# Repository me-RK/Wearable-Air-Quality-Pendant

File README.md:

Wearable Air Quality Pendant 🌬️
================================

A compact, battery-powered wearable device that continuously monitors air quality using TVOC detection. Get real-time feedback about your breathing environment through intuitive LED indicators and audio alerts.

Project Overview
-------------------

This DIY air quality monitor pendant uses professional-grade sensors to track Total Volatile Organic Compounds (TVOC) in real-time. Perfect for monitoring indoor air quality at home, office, or industrial environments.

### Key Features

-    **Real-time TVOC monitoring** using SGP40 sensor
-    **Ultra-low power design** with STM32U083KCU6 microcontroller
-    **Intuitive feedback** - Color-coded LEDs and musical alerts
-    **Wearable design** - Compact 32.5mm diameter pendant
-    **All-day battery life** with efficient power management
-    **Professional accuracy** with industrial-grade sensor

 Air Quality Classifications
------------------------------

| TVOC Level | Status | LED Color | Audio Alert |
| --- | --- | --- | --- |
| 0-200 | Good | 🟢 Green | Soft tone |
| 201-300 | Warning | 🟡 Yellow | Warning melody |
| 301-500 | Alarm | 🔴 Red | Urgent beeping |
| >500 | Error | 🔴 Flashing Red | Error tone |

 Hardware Components
-----------------------

### Main Components

-   **STM32U083KCU6** - Ultra-low-power microcontroller
-   **SGP40-D-R4** - Professional TVOC air quality sensor
-   **MCP73832T** - Li-Po battery charge controller
-   **ADPL44002** - Low-dropout voltage regulator
-   **EAST1616RGBA1** - RGB LEDs (4x)
-   **PKMCS0909E4000-R1** - Piezoelectric buzzer

### Power Management

-   Li-Po battery charging via USB-C
-   Regulated 2.5V supply for stable operation
-   Ultra-low power consumption for all-day use

📁 Repository Structure
-----------------------

```
├── Code/
│   └── Wearable_Air_Quality_Pendant/
│       ├── Wearable_Air_Quality_Pendant.ino
│       └── libraries/
├── PCB/
│   ├── Wearable-Air-Quality-Pendant.kicad_pro
│   ├── Schematic.pdf
│   └── Gerber_Files/
├── 3D_Models/
│   ├── Pendant_Top.stl
│   ├── Pendant_Bottom.stl
│   └── Assembly_Guide.pdf
├── Documentation/
│   ├── Circuit_Diagram.pdf
│   ├── Assembly_Instructions.pdf
│   └── BOM.csv
└── images/

```

🚀 Quick Start Guide
--------------------

### 1\. Hardware Assembly

1.  **Order PCB**: Use provided Gerber files
2.  **Solder components**: Follow the detailed BOM
3.  **3D print enclosure**: Use provided STL files
4.  **Assemble**: Insert PCB into printed enclosure

### 2\. Software Setup

1.  **Install Arduino IDE** (version 1.8.19 or newer)
2.  **Add STM32 board support**
3.  **Install required libraries**:
    -   DFRobot_SGP40
    -   PlayRtttl
    -   ptScheduler
4.  **Upload firmware** using ST-Link programmer

 Required Libraries
---------------------

Add these libraries through Arduino IDE Library Manager:

```
#include <DFRobot_SGP40.h>     // SGP40 sensor communication
#include <PlayRtttl.hpp>       // Musical tone generation
#include <ptScheduler.h>       // Non-blocking task scheduling

```

 Programming the Device
------------------------

### Hardware Requirements

-   **ST-Link V2 programmer** (required for STM32)
-   **USB-C cable** for power and charging
-   **3.3V power supply** during programming

### Upload Process

1.  Connect ST-Link to SWD pins (SWDIO, SWCLK)
2.  Select board: "STM32U0 series" in Arduino IDE
3.  Select programmer: "STM32CubeProgrammer (SWD)"
4.  Upload firmware

 PCB Specifications
---------------------

-   **Dimensions**: 32.5mm diameter
-   **Layers**: 2-layer PCB
-   **Thickness**: 1.6mm
-   **Components**: SMD (0603/0402 packages)
-   **Connector**: USB-C for charging

 3D Printing Guide
---------------------

### Print Settings

-   **Layer Height**: 0.2mm
-   **Infill**: 20%
-   **Supports**: Minimal (only for overhangs)
-   **Material**: PLA or PETG recommended

### Post-Processing

-   Light sanding for smooth finish
-   Ensure USB-C port alignment
-   Test fit before final assembly

Acknowledgments
------------------

-   **CircuitDigest** - Project development and documentation
-   **DFRobot** - SGP40 sensor library
-   **STMicroelectronics** - STM32 microcontroller support
-   **DigiKey** - Sponsors

Support
----------

-   **Detailed Tutorial**: [CircuitDigest Article](https://circuitdigest.com/videos/wearable-air-quality-pendant)
-   **Video Guide**: [YouTube Tutorial](https://youtube.com/watch?v=c5lP1kzYoBA)
-   **Issues**: Report bugs via GitHub Issues
-   **Discussion**: Join our community forum

Version History
-------------------

| Version | Date | Changes |
| --- | --- | --- |
| v1.0 | 2024-12 | Initial release |
| v1.1 | 2025-01 | Bug fixes, improved battery life |

* * * * *

**⭐ If this project helped you, please star the repository!**

**🔗 Related Projects:**

-   [Arduino Air Quality Monitor](https://github.com/Circuit-Digest/Arduino-Air-Quality-Monitor)
-   [IoT Air Quality System](https://github.com/Circuit-Digest/IoT-Air-Quality-System)

**📧 Contact:** support@circuitdigest.com

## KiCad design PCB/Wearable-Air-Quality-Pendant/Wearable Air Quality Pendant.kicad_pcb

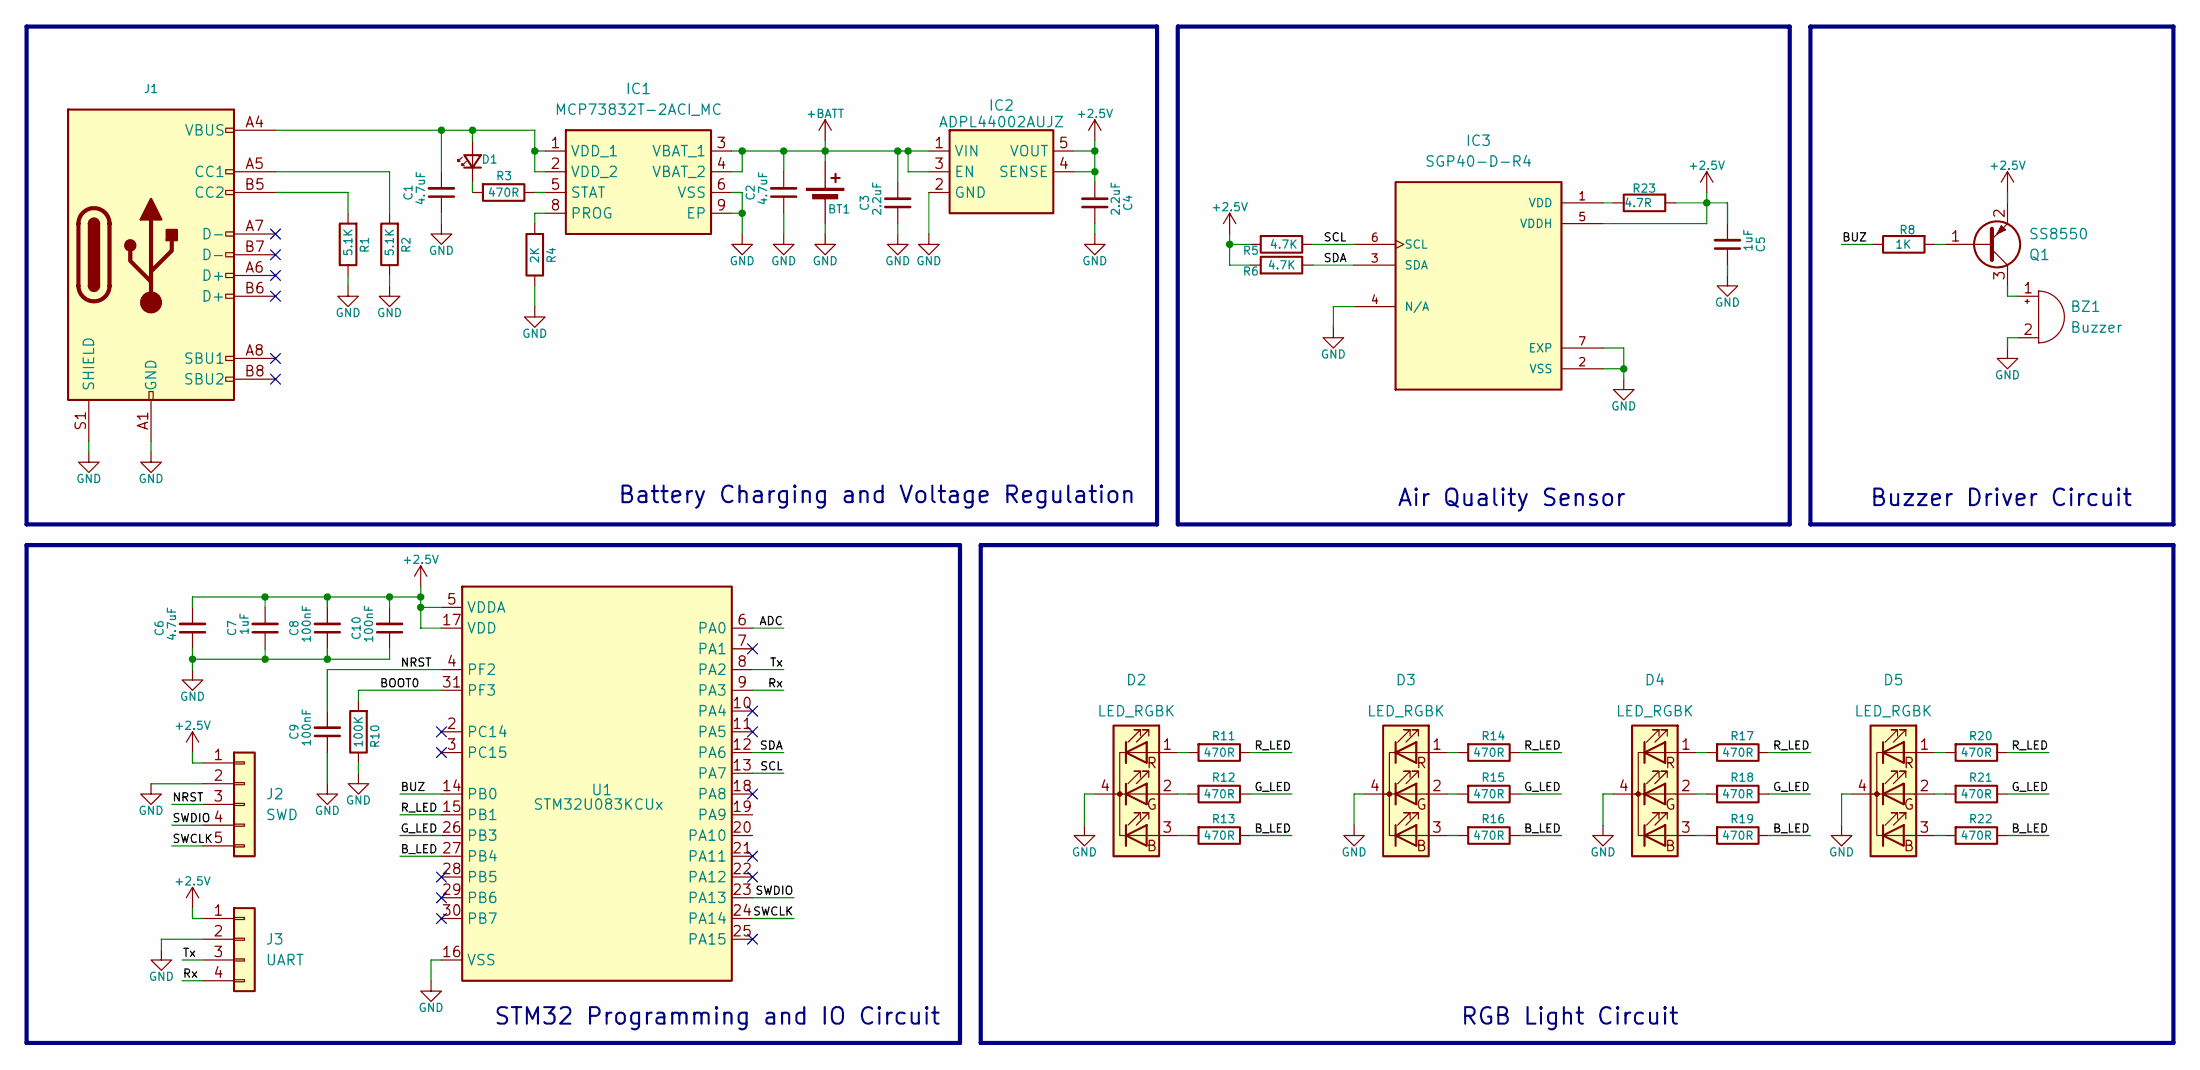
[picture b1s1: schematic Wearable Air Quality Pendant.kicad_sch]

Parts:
BT1: Battery_Cell; BAT_1060
BZ1: Buzzer; PKMCS0909E4000-R1_MUR
C1, C2, C6: 4.7uF; C_0603_1608Metric
C3, C4: 2.2uF; C_0603_1608Metric
C5, C7: 1uF; C_0603_1608Metric
C8, C9, C10: 100nF; C_0603_1608Metric
D1: LED_Small; LED_0603_1608Metric
D2, D3, D4, D5: LED_RGBK; EAST1616RGBA1
IC1: MCP73832T-2ACI_MC; SON50P300X200X100-9N-D; Mouser Part Number 579-MCP73832T-2ACIMC
IC2: ADPL44002AUJZ; SOT95P280X100-5N; Manufacturer_Part_Number ADPL44002AUJZ2.5-R7
IC3: SGP40-D-R4; XCDR_SGP40-D-R4; PARTREV 1.2
J1: USB_C_Receptacle_USB2.0_16P; USB_C_Receptacle_Palconn_UTC16-G
J2: SWD; PinHeader_1x06_P1.27mm_Vertical
J3: UART; PinHeader_1x04_P1.27mm_Vertical
Q1: SS8550; SOT-23
R1, R2: 5.1K; R_0603_1608Metric
R3, R11, R12, R13, R14, R15, R16, R17, R18, R19, R20, R21, R22: 470R; R_0603_1608Metric
R4: 2K; R_0603_1608Metric
R5, R6: 4.7K; R_0603_1608Metric
R8: 1K; R_0603_1608Metric
R10: 100K; R_0603_1608Metric
R23: 4.7R; R_0805_2012Metric
U1: STM32U083KCUx; QFN-32-1EP_5x5mm_P0.5mm_EP3.45x3.45mm

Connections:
+2.5V: C4.2, C5.2, C6.2, C7.2, C8.2, C10.2, IC2.4 (SENSE), IC2.5 (VOUT), IC3.5 (VDDH), J2.1, J3.1, Q1.2 (E), R5.2, R6.2, R23.2, U1.1 (VDD), U1.5 (VDDA), U1.17 (VDD)
+BATT: BT1.P (+), C2.2, C3.2, IC1.3 (VBAT_1), IC1.4 (VBAT_2), IC2.1 (VIN), IC2.3 (EN)
/ADC: U1.6 (PA0)
/BOOT0: R10.2, U1.31 (PF3)
/BUZ: R8.1, U1.14 (PB0)
/B_LED: R13.1, R16.1, R19.1, R22.1, U1.27 (PB4)
/G_LED: R12.1, R15.1, R18.1, R21.1, U1.26 (PB3)
/NRST: C9.2, J2.3, U1.4 (PF2)
/R_LED: R11.1, R14.1, R17.1, R20.1, U1.15 (PB1)
/Rx: J3.4, U1.9 (PA3)
/SCL: IC3.6 (SCL), R5.1, U1.13 (PA7)
/SDA: IC3.3 (SDA), R6.1, U1.12 (PA6)
/SWCLK: J2.5, U1.24 (PA14)
/SWDIO: J2.4, U1.23 (PA13)
/Tx: J3.3, U1.8 (PA2)
GND: BT1.N (-), BZ1.2 (-), C1.1, C2.1, C3.1, C4.1, C5.1, C6.1, C7.1, C8.1, C9.1, C10.1, D2.4 (K), D3.4 (K), D4.4 (K), D5.4 (K), IC1.6 (VSS), IC1.9 (EP), IC2.2 (GND), IC3.2 (VSS), IC3.4 (N/A), IC3.7 (EXP), J1.A1 (GND), J1.A12 (GND), J1.B1 (GND), J1.B12 (GND), J1.S1 (SHIELD), J2.2, J3.2, R1.1, R2.1, R4.1, R10.1, U1.16 (VSS), U1.32 (VSS), U1.33 (VSS)
unnamed: BZ1.1 (+), Q1.3 (C)
unnamed: C1.2, D1.2 (A), IC1.1 (VDD_1), IC1.2 (VDD_2), J1.A4 (VBUS), J1.A9 (VBUS), J1.B4 (VBUS), J1.B9 (VBUS)
unnamed: D1.1 (K), R3.2
unnamed: D2.3 (BA), R13.2
unnamed: D2.2 (GA), R12.2
unnamed: D2.1 (RA), R11.2
unnamed: D3.3 (BA), R16.2
unnamed: D3.2 (GA), R15.2
unnamed: D3.1 (RA), R14.2
unnamed: D4.3 (BA), R19.2
unnamed: D4.2 (GA), R18.2
unnamed: D4.1 (RA), R17.2
unnamed: D5.3 (BA), R22.2
unnamed: D5.2 (GA), R21.2
unnamed: D5.1 (RA), R20.2
unnamed: IC1.8 (PROG), R4.2
unnamed: IC1.5 (STAT), R3.1
unnamed: IC3.1 (VDD), R23.1
unnamed: J1.A5 (CC1), R2.2
unnamed: J1.B5 (CC2), R1.2
unnamed: Q1.1 (B), R8.2

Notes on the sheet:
Air Quality Sensor
STM32 Programming and IO Circuit
Battery Charging and Voltage Regulation
RGB Light Circuit
Buzzer Driver Circuit

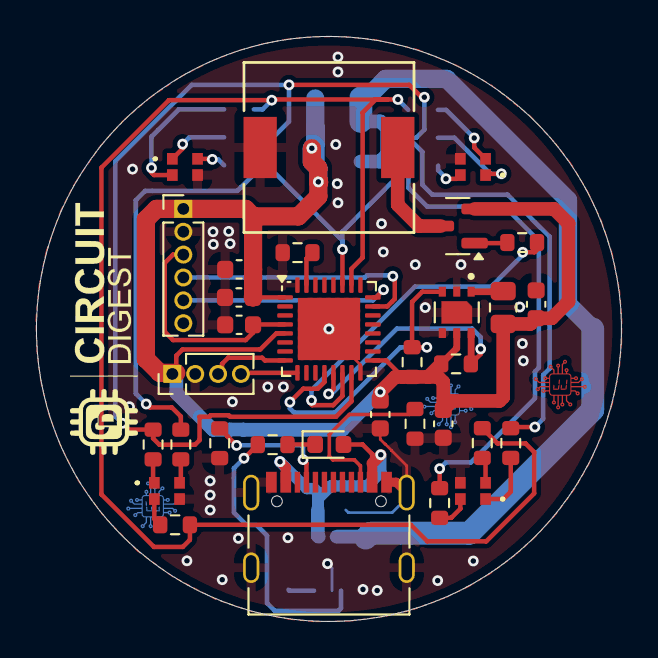
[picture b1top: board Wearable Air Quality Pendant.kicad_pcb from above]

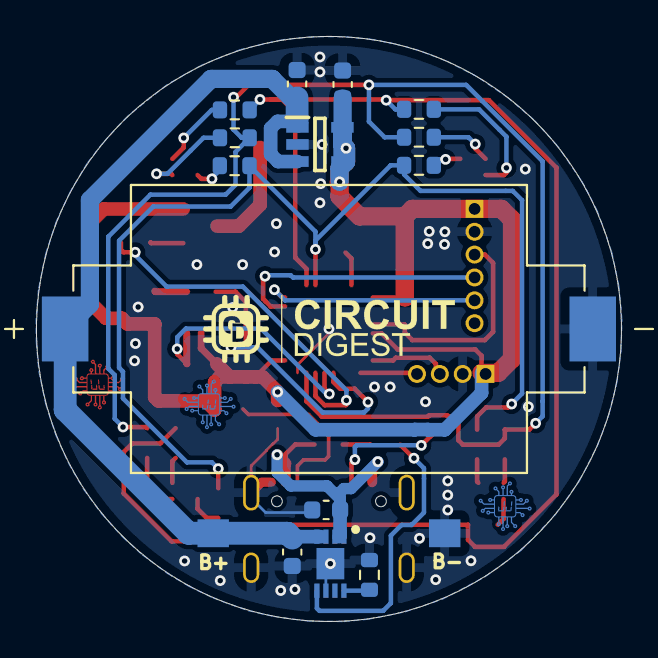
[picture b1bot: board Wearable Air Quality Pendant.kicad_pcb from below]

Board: 2 copper layers, 32.5 x 32.5 mm, 46 parts (14 on the bottom side), 36 nets.

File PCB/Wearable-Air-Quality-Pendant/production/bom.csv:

Designator,Footprint,Quantity,Value,LCSC Part #
"_2, ",,2,,
BT1,BAT_1060,1,Battery_Cell,
BZ1,PKMCS0909E4000-R1_MUR,1,Buzzer,
"C1, C2, C6",0603,3,4.7uF,
"C10, C8, C9",0603,3,100nF,
"C3, C4",0603,2,2.2uF,
"C5, C7",0603,2,1uF,
D1,0603,1,LED_Small,
"D2, D3, D4, D5",EAST1616RGBA1,4,LED_RGBK,
IC1,SON50P300X200X100-9N-D,1,MCP73832T-2ACI_MC,
IC2,SOT95P280X100-5N,1,ADPL44002AUJZ,
IC3,XCDR_SGP40-D-R4,1,SGP40-D-R4,
J1,USB_C_Receptacle_Palconn_UTC16-G,1,USB_C_Receptacle_USB2.0_16P,
J2,PinHeader_1x06_P1.27mm_Vertical,1,SWD,
J3,PinHeader_1x04_P1.27mm_Vertical,1,UART,
Q1,SOT-23,1,SS8550,
"R1, R2",0603,2,5.1K,
R10,0603,1,100K,
"R11, R12, R13, R14, R15, R16, R17, R18, R19, R20, R21, R22, R3",0603,13,470R,
R23,0805,1,4.7R,
R4,0603,1,2K,
"R5, R6",0603,2,4.7K,
R8,0603,1,1K,
U1,QFN-32-1EP_5x5mm_P0.5mm_EP3.45x3.45mm,1,STM32U083KCUx,

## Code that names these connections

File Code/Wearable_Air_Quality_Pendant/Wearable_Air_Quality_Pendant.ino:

/*
  =======================================================================
  Project: Air Quality Monitor with TVOC Index using SGP40 Sensor

  Features:
  - Reads Total Volatile Organic Compounds (TVOC) index from SGP40 sensor
  - Indicates air quality using LEDs (Red, Green) with smooth fading effect
  - Plays RTTTL tone alerts for different air quality levels via buzzer
  - Displays TVOC values via LPUART serial (PA2, PA3)
  - Shows error states with visual (LED) and audible (buzzer) indication

  Working:
  - SGP40 sensor periodically reads TVOC index
  - Based on the index value, system classifies air as:
      0–200   → Good (Soft tone, Green LED)
      201–300 → Warning (Warn tone, Yellow LED)
      301–500 → Alarm (Alarm tone, Red LED)
  - If TVOC exceeds 500 or sensor fails, Error tone & Red LED flash
  - Scheduler ensures non-blocking periodic sensor read, LED updates, and sound
  =======================================================================
*/

#include <DFRobot_SGP40.h> // need to install
#include <HardwareSerial.h>
#include <Arduino.h>
#include <PlayRtttl.hpp> // need to install
#include <ptScheduler.h> // need to install

// LED and Buzzer pin definitions
#define RED_PIN PB3
#define GREEN_PIN PB4
#define BUZZER_PIN PB0

// Define serial on PA3 (RX) and PA2 (TX)
HardwareSerial MyLPUART1(PA3, PA2);

// Create SGP40 sensor object
DFRobot_SGP40 mySgp40;

// Variables for tone request and fading effect
int tvoc = 0;
int toneRequest = -1;
int fadeStep = 0;

// Time tracking variables for non-blocking operations
unsigned long prevLedTime = 0;
unsigned long prevToneTime = 0;

// Define RTTTL tone melodies
const char softTone[] = "Soft:d=8,o=5,b=100:g";
const char warnTone[] = "Warn:d=4,o=5,b=120:c,e,g";
const char alarmTone[] = "Alarm:d=16,o=5,b=180:c6,c6,c6";
const char startTone[] = "Start:d=8,o=6,b=120:c,e,g";
const char errorTone[] = "Error:d=4,o=5,b=160:c,c,r,c";

// Enum to associate tone types with time intervals
enum ToneType {
  TONE_SOFT = 5000,
  TONE_WARN = 2000,
  TONE_ALARM = 500,
  TONE_START = 1000,
  TONE_ERROR = 200
};

// Task scheduler for non-blocking periodic functions
ptScheduler readSensorTask(PT_TIME_1S);   // Sensor reading every 1 second
ptScheduler lightTask(PT_TIME_100MS);     // LED update task
ptScheduler soundTask(PT_TIME_100MS);     // Buzzer task

// Function declarations
void playTone(ToneType tone);
void updateLedFade(ToneType tone);
void showErrorState();
void readAndEvaluateAir();

void setup() {
  MyLPUART1.begin(115200);

  // Initialize output pins
  pinMode(RED_PIN, OUTPUT);
  pinMode(GREEN_PIN, OUTPUT);
  pinMode(BUZZER_PIN, OUTPUT);

  MyLPUART1.println("sgp40 is starting, the reading can be taken after 10 seconds...");

  // Startup indication
  updateLedFade(TONE_START);
  playTone(TONE_START);

  // Initialize sensor
  if (!mySgp40.begin(10000)) {
    MyLPUART1.println("Failed to init chip. Please check connection.");
    showErrorState();
    while (true);  // Stop execution on failure
  }

  MyLPUART1.println("sgp40 initialized successfully!");
}

void loop() {
  // Periodically read sensor
  if (readSensorTask.call()) {
    readAndEvaluateAir();
  }

  // Update LED fading effect based on tone
  if (lightTask.call() && toneRequest != -1) {
    updateLedFade((ToneType)toneRequest);
  }

  // Play tone based on tone request
  if (soundTask.call() && toneRequest != -1 && toneRequest != TONE_SOFT) {
    playTone((ToneType)toneRequest);
  }
}

// Reads TVOC value and determines air quality level
void readAndEvaluateAir() {
  tvoc = mySgp40.getVoclndex();

  MyLPUART1.print("vocIndex = ");
  MyLPUART1.println(tvoc);

  if (tvoc <= 200) {
    toneRequest = TONE_SOFT;
  } else if (tvoc <= 300) {
    toneRequest = TONE_WARN;
  } else if (tvoc <= 500) {
    toneRequest = TONE_ALARM;
  } else {
    MyLPUART1.println("Invalid TVOC value.");
    showErrorState();
  }
}

// Smooth LED fading based on tone type
void updateLedFade(ToneType tone) {
  static const int maxBrightness = 255;
  static const int fadeSpeed = 5;
  static const int fadeDelay = 10;

  unsigned long currentMillis = millis();
  if (currentMillis - prevToneTime < tone) return;
  prevToneTime = currentMillis;

  int redTarget = 0, greenTarget = 0;

  // Set target brightness levels based on tone
  switch (tone) {
    case TONE_SOFT: greenTarget = maxBrightness; break;                  // Green only
    case TONE_WARN: redTarget = greenTarget = maxBrightness; break;     // Yellow (Red + Green)
    case TONE_ALARM:
    case TONE_ERROR: redTarget = maxBrightness; break;                  // Red only
    default: break;
  }

  // Fade in
  for (int brightness = 0; brightness <= 255; brightness += fadeSpeed) {
    analogWrite(RED_PIN, (brightness * redTarget) / 255);
    analogWrite(GREEN_PIN, (brightness * greenTarget) / 255);
    delay(fadeDelay);
  }

  // Fade out
  for (int brightness = 255; brightness >= 0; brightness -= fadeSpeed) {
    analogWrite(RED_PIN, (brightness * redTarget) / 255);
    analogWrite(GREEN_PIN, (brightness * greenTarget) / 255);
    delay(fadeDelay);
  }

  // Reset if loop exceeds max fade cycle
  fadeStep += fadeSpeed;
  if (fadeStep > 510) {
    analogWrite(RED_PIN, 0);
    analogWrite(GREEN_PIN, 0);
  }
}

// Play a tone melody corresponding to the tone type
void playTone(ToneType tone) {
  unsigned long currentMillis = millis();
  if (currentMillis - prevLedTime < tone) return;
  prevLedTime = currentMillis;

  switch (tone) {
    case TONE_SOFT:  playRtttlBlockingPGM(BUZZER_PIN, softTone); break;
    case TONE_WARN:  playRtttlBlockingPGM(BUZZER_PIN, warnTone); break;
    case TONE_ALARM: playRtttlBlockingPGM(BUZZER_PIN, alarmTone); break;
    case TONE_START: playRtttlBlockingPGM(BUZZER_PIN, startTone); break;
    case TONE_ERROR: playRtttlBlockingPGM(BUZZER_PIN, errorTone); break;
  }
}

// Show error condition using LED and buzzer
void showErrorState() {
  toneRequest = TONE_ERROR;
  soundTask.enable();
}
